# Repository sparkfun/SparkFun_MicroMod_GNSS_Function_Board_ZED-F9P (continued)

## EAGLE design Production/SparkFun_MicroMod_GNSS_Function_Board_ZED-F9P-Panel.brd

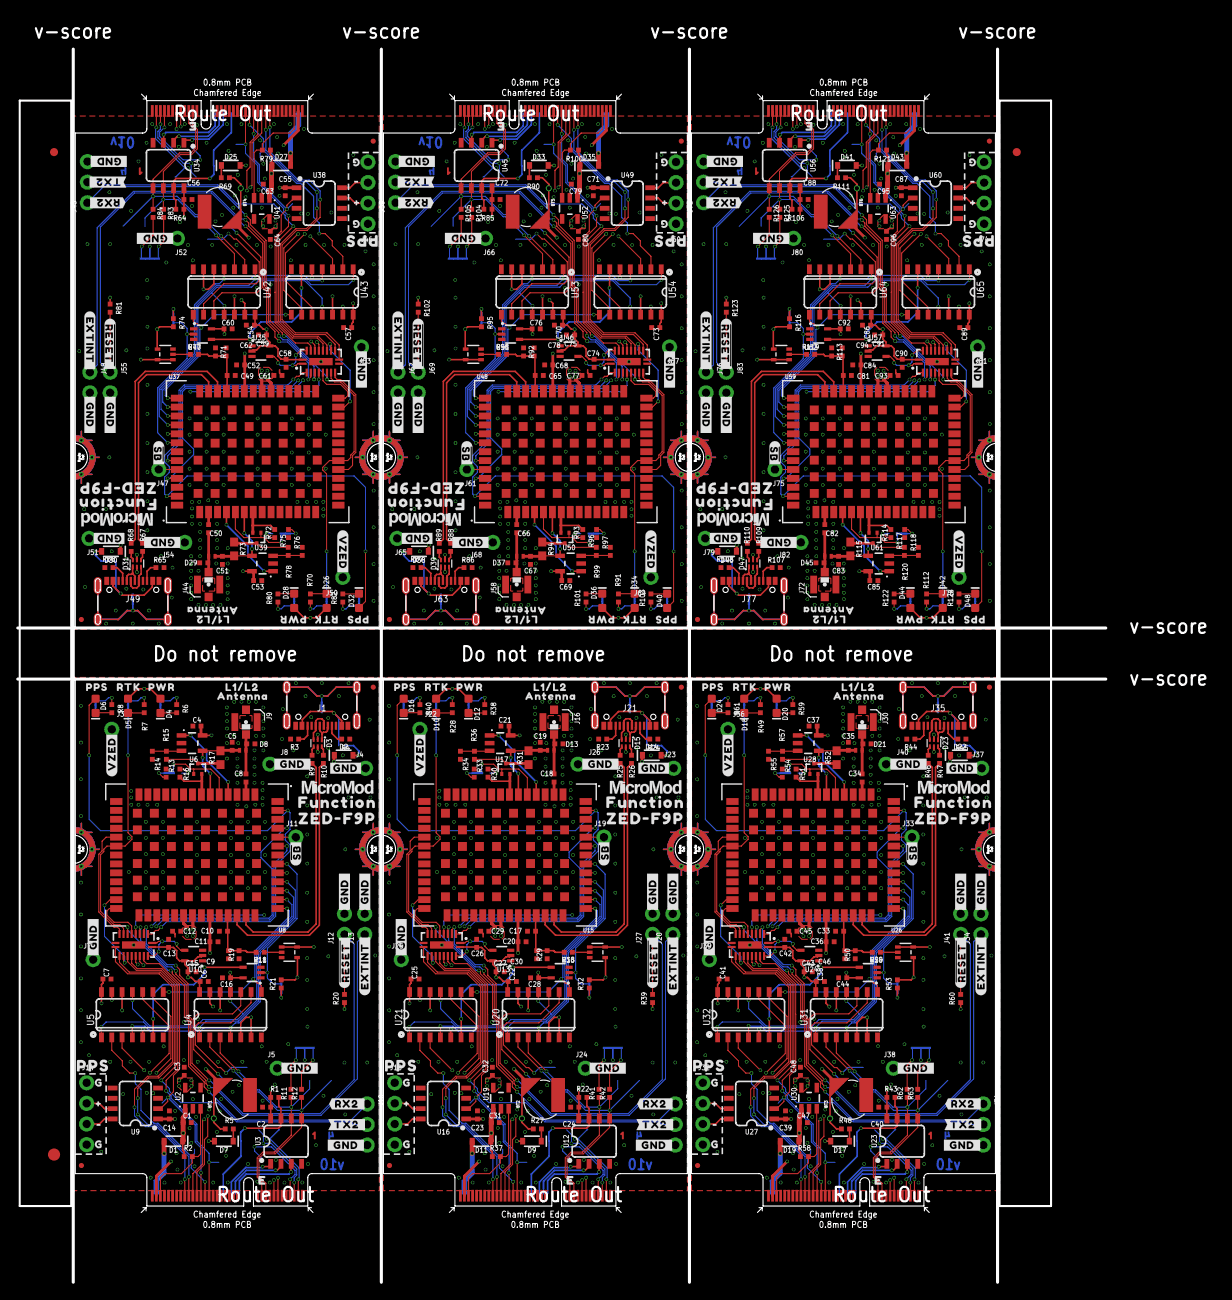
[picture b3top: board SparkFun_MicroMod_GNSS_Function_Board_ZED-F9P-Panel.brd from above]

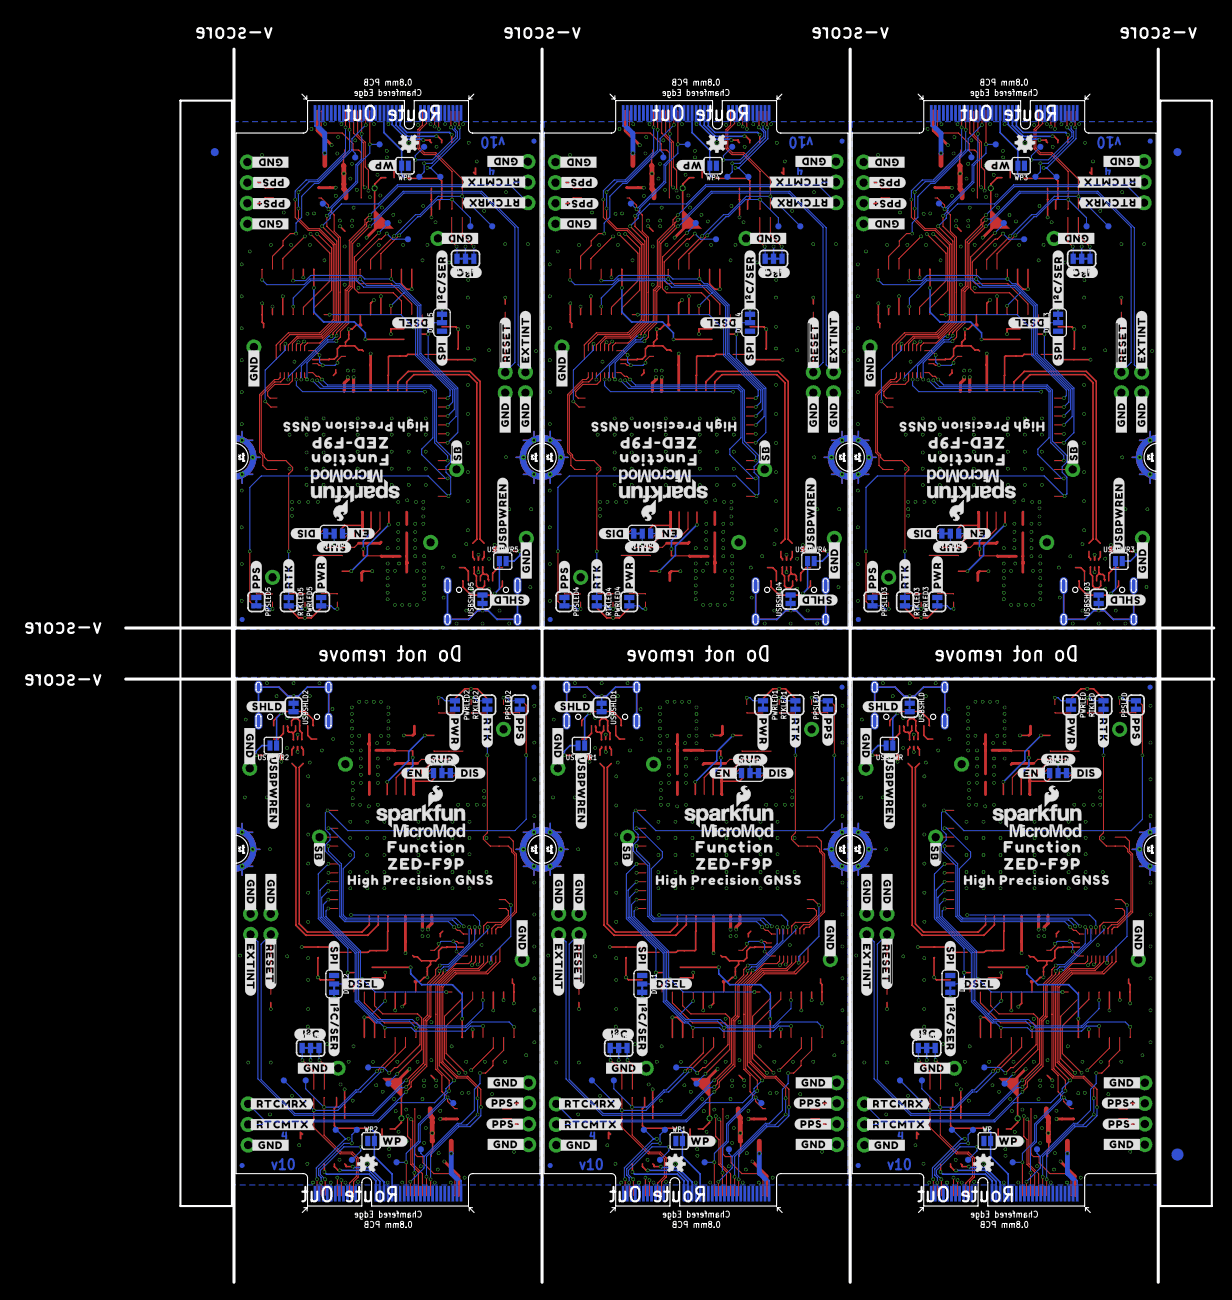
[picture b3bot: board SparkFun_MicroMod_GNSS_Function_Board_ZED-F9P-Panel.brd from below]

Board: 4 copper layers, 134.2 x 152.1 mm, 984 parts (339 on the bottom side), 468 nets.

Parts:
ANTSUP, ANTSUP1, ANTSUP2, ANTSUP3, ANTSUP4, ANTSUP5: JUMPER-SMT_3_1-NC_TRACE_SILK; SMT-JUMPER_3_1-NC_TRACE_SILK
BT1, BT2, BT3, BT4, BT5, BT6: RELOWABLE_BATTERY_MS421R; MS421R_IV03E
C1, C3, C9, C12, C29, C30, C31, C32, C45, C46, C47, C48, C61, C62, C63, C64, C77, C78, C79, C80, C93, C94, C95, C96: 1.0uF; 0402-TIGHT
C2, C4, C6, C7, C10, C13, C14, C15, C16, C17, C21, C22, C23, C24, C25, C26, C27, C28, C33, C37, C38, C39, C40, C41, C42, C43, C44, C49, C53, C54, C55, C56, C57, C58, C59, C60, C65, C69, C70, C71, C72, C73, C74, C75, C76, C81, C85, C86, C87, C88, C89, C90, C91, C92: 0.1uF; 0402-TIGHT
C5, C19, C35, C51, C67, C83: 10nF; 0402-TIGHT
C8, C18, C34, C50, C66, C82: 47pF; 0402-TIGHT
C11, C20, C36, C52, C68, C84: 2.2uF; 0402-TIGHT
D1, D2, D11, D14, D19, D22, D27, D30, D35, D38, D43, D46: 3A/10V/280mV; SOD-323
D3, D15, D23, D31, D39, D47: PRTR5V0U2F; SOT886
D4, D12, D20, D28, D36, D44: RED; LED-0603
D5, D6, D10, D16, D18, D24, D26, D32, D34, D40, D42, D48: BLUE; LED-0603
D7, D9, D17, D25, D33, D41: 0.5A/40V/420mV; SOD-323
D8, D13, D21, D29, D37, D45: PESD0402-0402T; 0402-TIGHT
DSEL, DSEL1, DSEL2, DSEL3, DSEL4, DSEL5: JUMPER-SMT_3_1-NC_TRACE_SILK; SMT-JUMPER_3_1-NC_TRACE_SILK
E$1, E$2, E$3, E$4: FIDUCIAL-1X2
E$5, E$6: FIDUCIAL-1.5X3
FD1, FD2, FD3, FD4, FD5, FD6, FD7, FD8, FD9, FD10, FD11, FD12, FD13, FD14, FD15, FD16, FD17, FD18, FD19, FD20, FD21, FD22, FD23, FD24: FIDUCIALUFIDUCIAL; FIDUCIAL-MICRO
FRAME1, FRAME2, FRAME3, FRAME4, FRAME5, FRAME6: FRAME-LEDGER; CREATIVE_COMMONS
I2CPUR, I2CPUR1, I2CPUR2, I2CPUR3, I2CPUR4, I2CPUR5: JUMPER-SMT_3_2-NC_TRACE_SILK; SMT-JUMPER_3_2-NC_TRACE_SILK
J1, J21, J35, J49, J63, J77: USB Female Type C Connector; USB-C-16P-4LAYER-ISOLATED
J2, J15, J29, J43, J57, J71: MICROMOD_FUNCTION_STANDARD; M.2-CARD-E-22_FUNCTION_STANDARD
J3, J4, J5, J7, J8, J11, J19, J22, J23, J24, J25, J26, J33, J36, J37, J38, J39, J40, J47, J50, J51, J52, J53, J54, J61, J64, J65, J66, J67, J68, J75, J78, J79, J80, J81, J82: 1X01_NO_SILK
J6, J28, J42, J56, J70, J84: 1X01_SMALL
J9, J16, J30, J44, J58, J72: U.FL
J10, J17, J31, J45, J59, J73: 455-1750-1-ND; 1X03_NO_SILK
J12, J13, J20, J27, J34, J41, J48, J55, J62, J69, J76, J83: 1X02_NO_SILK
J14, J18, J32, J46, J60, J74: 1X04_NO_SILK
L1, L2, L3, L4, L5, L6: 150nH; 0402_MURATA
LOGO1, LOGO6, LOGO9, LOGO12, LOGO15, LOGO18: SFE_LOGO_NAME_FLAMEBLANK; BLANK
LOGO2, LOGO3, LOGO7, LOGO10, LOGO13, LOGO16: OSHW-LOGOMINI; OSHW-LOGO-MINI
LOGO4, LOGO5, LOGO8, LOGO11, LOGO14, LOGO17: SFE_LOGO_NAME_FLAME.1_INCH; SFE_LOGO_NAME_FLAME_.1
PPSLED, PPSLED1, PPSLED2, PPSLED3, PPSLED4, PPSLED5: JUMPER-SMT_2_NC_TRACE_SILK; SMT-JUMPER_2_NC_TRACE_SILK
PWRLED, PWRLED1, PWRLED2, PWRLED3, PWRLED4, PWRLED5: JUMPER-SMT_2_NC_TRACE_SILK; SMT-JUMPER_2_NC_TRACE_SILK
Q1, Q2, Q3, Q4, Q5, Q6: DMP21D0UT-7; SOT523
R1, R2, R13, R14, R20, R21, R22, R32, R33, R34, R37, R39, R43, R53, R54, R55, R58, R60, R64, R74, R75, R76, R79, R81, R85, R95, R96, R97, R100, R102, R106, R116, R117, R118, R121, R123: 10k; 0402-TIGHT
R3, R4, R23, R24, R44, R45, R65, R66, R86, R87, R107, R108: 5.1k; 0402-TIGHT
R5, R27, R48, R69, R90, R111: 3.3K; 0402-TIGHT
R6, R15, R36, R38, R57, R59, R78, R80, R99, R101, R120, R122: 1k; 0402-TIGHT
R7, R8, R28, R40, R49, R61, R70, R82, R91, R103, R112, R124: 4.7k; 0402-TIGHT
R9, R10, R25, R26, R46, R47, R67, R68, R88, R89, R109, R110: 27; 0402-TIGHT
R11, R12, R41, R42, R62, R63, R83, R84, R104, R105, R125, R126: 2.2k; 0402-TIGHT
R16, R30, R51, R72, R93, R114: 100k; 0402-TIGHT
R17, R31, R52, R73, R94, R115: 10; 0603
R18, R35, R56, R77, R98, R119: 22k; 0402-TIGHT
R19, R29, R50, R71, R92, R113: 47k; 0402-TIGHT
RTKLED, RTKLED1, RTKLED2, RTKLED3, RTKLED4, RTKLED5: JUMPER-SMT_2_NC_TRACE_SILK; SMT-JUMPER_2_NC_TRACE_SILK
TP1, TP2, TP3, TP4, TP5, TP6, TP7, TP8, TP9, TP10, TP11, TP12, TP13, TP14, TP15, TP16, TP17, TP18, TP19, TP20, TP21, TP22, TP23, TP24, TP25, TP26, TP27, TP28, TP29, TP30, TP31, TP32, TP33, TP34, TP35, TP36, TP37, TP38, TP39, TP40, TP41, TP42, TP43, TP44, TP45, TP46, TP47, TP48, TP49, TP50, TP51, TP52, TP53, TP54, TP55, TP56, TP57, TP58, TP59, TP60: TEST-POINT3; PAD.03X.03
U1, U22, U33, U44, U55, U66: NLAST4501DFT2G; SOT353
U2, U19, U30, U41, U52, U63: 3.3V; SOT23-5
U3, U12, U23, U34, U45, U56: EEPROM; SO08
U4, U5, U20, U21, U31, U32, U42, U43, U53, U54, U64, U65: 74LVC4066D_QUAD_BILATERAL_SWITCH; SO14
U6, U17, U28, U39, U50, U61: OPA344; SOT23-5
U7, U14, U25, U36, U47, U58: 74LVC541A; DHVQFN20
U8, U15, U26, U37, U48, U59: U-BLOX_ZED-F9P; ZED-F9P
U9, U16, U27, U38, U49, U60: FIN1017MX; SO08
U10, U11, U13, U18, U24, U29, U35, U40, U46, U51, U57, U62: SN74AUP1T04; SC-70-5_DCK
U$1, U$119, U$182, U$245, U$308, U$371: 40
U$2, U$92, U$159, U$222, U$285, U$348: #_RTCMTX#0
U$3, U$93, U$160, U$223, U$286, U$349: #TX2_#0
U$4, U$8, U$37, U$63, U$127, U$128, U$190, U$191, U$253, U$254, U$316, U$317: MICROMOD_LOGO_.35
U$5, U$6, U$7, U$9, U$10, U$11, U$18, U$19, U$21, U$22, U$25, U$33, U$38, U$39, U$94, U$95, U$96, U$97, U$98, U$99, U$108, U$109, U$110, U$111, U$116, U$123, U$124, U$125, U$161, U$162, U$163, U$164, U$165, U$166, U$173, U$174, U$175, U$176, U$179, U$186, U$187, U$188, U$224, U$225, U$226, U$227, U$228, U$229, U$236, U$237, U$238, U$239, U$242, U$249, U$250, U$251, U$287, U$288, U$289, U$290, U$291, U$292, U$299, U$300, U$301, U$302, U$305, U$312, U$313, U$314, U$350, U$351, U$352, U$353, U$354, U$355, U$362, U$363, U$364, U$365, U$368, U$375, U$376, U$377: #_GND_#0
U$12, U$100, U$167, U$230, U$293, U$356: #_RTCMRX#0
U$13, U$101, U$168, U$231, U$294, U$357: #RX2_#0
U$14, U$102, U$169, U$232, U$295, U$358: ##RESET_##0
U$15, U$103, U$170, U$233, U$296, U$359: #_#RESET##0
U$16, U$105, U$171, U$234, U$297, U$360: #_EXTINT#0
U$17, U$107, U$172, U$235, U$298, U$361: #EXTINT_#0
U$20, U$26, U$27, U$41, U$129, U$130, U$192, U$193, U$255, U$256, U$318, U$319: FUNCTION0
U$23, U$113, U$177, U$240, U$303, U$366: #_I�C#SER#0
U$24, U$115, U$178, U$241, U$304, U$367: #SPI_#0
U$28, U$117, U$180, U$243, U$306, U$369: #_I�C#0
U$29, U$118, U$181, U$244, U$307, U$370: #_DSEL#0
U$30, U$120, U$183, U$246, U$309, U$372: #SUP#0
U$31, U$121, U$184, U$247, U$310, U$373: #RTK#0
U$32, U$122, U$185, U$248, U$311, U$374: #PWR#0
U$34, U$42, U$131, U$194, U$257, U$320: 10
U$35, U$43, U$132, U$195, U$258, U$321: 211
U$36, U$53, U$133, U$196, U$259, U$322: 3212
U$40, U$126, U$189, U$252, U$315, U$378: PPS3
U$44, U$60, U$139, U$202, U$265, U$328: #PPS##2252
U$45, U$61, U$140, U$203, U$266, U$329: #PPS##2253
U$46, U$47, U$55, U$56, U$134, U$135, U$197, U$198, U$260, U$261, U$323, U$324: G2
U$48, U$57, U$136, U$199, U$262, U$325: #3
U$49, U$58, U$137, U$200, U$263, U$326: #4
U$50, U$65, U$141, U$204, U$267, U$330: #PPS#2254
U$51, U$66, U$142, U$205, U$268, U$331: PPS0
U$52, U$67, U$143, U$206, U$269, U$332: RTK0
U$54, U$81, U$151, U$214, U$277, U$340: #WP#0
U$59, U$104, U$138, U$201, U$264, U$327: SFE_LOGO_FLAME_STOP_.1
U$62, U$70, U$145, U$208, U$271, U$334: #USBPWREN#10
U$64, U$71, U$146, U$209, U$272, U$335: #SHLD#12
U$68, U$89, U$156, U$219, U$282, U$345: #VZED#0
U$69, U$76, U$144, U$207, U$270, U$333: ##SB##9
U$72, U$79, U$150, U$213, U$276, U$339: PWR0
U$73, U$90, U$157, U$220, U$283, U$346: #_DIS#0
U$74, U$91, U$158, U$221, U$284, U$347: #EN_#0
U$75, U$106, U$147, U$210, U$273, U$336: HIGH_PRECISION_GNSS26
U$77, U$78, U$112, U$114, U$148, U$149, U$211, U$212, U$274, U$275, U$337, U$338: ZED#F9P0
U$80, U$83, U$152, U$215, U$278, U$341: ##SB##0
U$82, U$84, U$153, U$216, U$279, U$342: #GND#0
U$85, U$86, U$154, U$217, U$280, U$343: L1#L20
U$87, U$88, U$155, U$218, U$281, U$344: ANTENNA0
USBPWR, USBPWR1, USBPWR2, USBPWR3, USBPWR4, USBPWR5: JUMPER-SMT_2_NO_SILK; SMT-JUMPER_2_NO_SILK
USBSHLD, USBSHLD1, USBSHLD2, USBSHLD3, USBSHLD4, USBSHLD5: JUMPER-SMT_2_NC_TRACE_SILK; SMT-JUMPER_2_NC_TRACE_SILK
WP, WP1, WP2, WP3, WP4, WP5: JUMPER-SMT_2_NO_SILK; SMT-JUMPER_2_NO_SILK

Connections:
3.3V: C2.1, C14.1, D7.A, J2.73, R1.1, U3.8, U9.1
3.3V1: C23.1, C24.1, D9.A, J15.73, R22.1, U12.8, U16.1
3.3V2: C39.1, C40.1, D17.A, J29.73, R43.1, U23.8, U27.1
3.3V3: C55.1, C56.1, D25.A, J43.73, R64.1, U34.8, U38.1
3.3V4: C71.1, C72.1, D33.A, J57.73, R85.1, U45.8, U49.1
3.3V5: C87.1, C88.1, D41.A, J71.73, R106.1, U56.8, U60.1
5V: C1.1, D1.C, D2.C, R2.1, U2.1
5V1: C31.1, D11.C, D14.C, R37.1, U19.1
5V2: C47.1, D19.C, D22.C, R58.1, U30.1
5V3: C63.1, D27.C, D30.C, R79.1, U41.1
5V4: C79.1, D35.C, D38.C, R100.1, U52.1
5V5: C95.1, D43.C, D46.C, R121.1, U63.1
!RESET!: J2.53, J12.1, R20.2, U7.3
!RESET!1: J15.53, J27.1, R39.2, U14.3
!RESET!2: J29.53, J41.1, R60.2, U25.3
!RESET!3: J43.53, J55.1, R81.2, U36.3
!RESET!4: J57.53, J69.1, R102.2, U47.3
!RESET!5: J71.53, J83.1, R123.2, U58.3
!ZED_DSEL!: U5.5, U5.6, U5.12, U5.13, U11.4
!ZED_DSEL!1: U18.4, U21.5, U21.6, U21.12, U21.13
!ZED_DSEL!2: U29.4, U32.5, U32.6, U32.12, U32.13
!ZED_DSEL!3: U40.4, U43.5, U43.6, U43.12, U43.13
!ZED_DSEL!4: U51.4, U54.5, U54.6, U54.12, U54.13
!ZED_DSEL!5: U62.4, U65.5, U65.6, U65.12, U65.13
A0: J2.36, U3.1
A1: J2.34, U3.2
A2: J2.32, U3.3
A3: J15.36, U12.1
A4: J15.32, U12.3
A5: J15.34, U12.2
A6: J29.36, U23.1
A7: J29.32, U23.3
A8: J29.34, U23.2
A9: J43.36, U34.1
A10: J43.32, U34.3
A11: J43.34, U34.2
A12: J57.36, U45.1
A13: J57.32, U45.3
A14: J57.34, U45.2
A15: J71.36, U56.1
A16: J71.32, U56.3
A17: J71.34, U56.2
EWP: J2.40, R1.2, U3.7, WP.2
EWP1: J15.40, R22.2, U12.7, WP1.2
EWP2: J29.40, R43.2, U23.7, WP2.2
EWP3: J43.40, R64.2, U34.7, WP3.2
EWP4: J57.40, R85.2, U45.7, WP4.2
EWP5: J71.40, R106.2, U56.7, WP5.2
EXTINT: J2.55, J13.1, U7.4
EXTINT1: J15.55, J20.1, U14.4
EXTINT2: J29.55, J34.1, U25.4
EXTINT3: J43.55, J48.1, U36.4
EXTINT4: J57.55, J62.1, U47.4
EXTINT5: J71.55, J76.1, U58.4
GEO_STAT: J2.59, U7.11
GEO_STAT1: J15.59, U14.11
GEO_STAT2: J29.59, U25.11
GEO_STAT3: J43.59, U36.11
GEO_STAT4: J57.59, U47.11
GEO_STAT5: J71.59, U58.11
GND: BT1.-, C1.2, C2.2, C3.2, C4.2, C5.2, C6.2, C7.2, C9.2, C10.2, C11.2, C12.2, C13.2, C14.2, C15.2, C16.2, D3.2, D8.2, DSEL.1, J1.GND, J1.GND2, J2.1, J2.33, J2.39, J2.45, J2.75, J2.GND1, J2.GND2, J2.GND3, J2.GND4, J2.GND5, J2.GND6, J4.1, J5.1, J7.1, J8.1, J9.1, J9.2, J10.3, J12.2, J13.2, J14.1, J14.4, PPSLED.1, PWRLED.2, R3.1, R4.1, R14.1, R16.1, R19.1, U1.3, U2.2, U3.4, U4.7, U5.7, U6.2, U7.10, U7.EPAD, U8.1, U8.3, U8.12, U8.14, U8.32, U8.37, U8.41, U8.48, U8.55, U8.56, U8.57, U8.58, U8.59, U8.60, U8.61, U8.62, U8.63, U8.64, U8.65, U8.66, U8.67, U8.68, U8.69, U8.70, U8.71, U8.72, U8.73, U8.74, U8.75, U8.76, U8.77, U8.78, U8.79, U8.80, U8.81, U8.82, U8.83, U8.84, U8.85, U8.86, U8.87, U8.88, U8.89, U8.90, U8.91, U8.92, U8.93, U8.94, U8.95, U8.96, U8.97, U8.98, U8.99, U8.100, U8.101, U8.102, U9.4, U10.3, U11.3, USBSHLD.2, WP.1
GND1: BT2.-, C17.2, C19.2, C20.2, C21.2, C22.2, C23.2, C24.2, C25.2, C26.2, C27.2, C28.2, C29.2, C30.2, C31.2, C32.2, D13.2, D15.2, DSEL1.1, J15.1, J15.33, J15.39, J15.45, J15.75, J15.GND1, J15.GND2, J15.GND3, J15.GND4, J15.GND5, J15.GND6, J16.1, J16.2, J17.3, J18.1, J18.4, J20.2, J21.GND, J21.GND2, J23.1, J24.1, J25.1, J26.1, J27.2, PPSLED1.1, PWRLED1.2, R23.1, R24.1, R29.1, R30.1, R34.1, U12.4, U13.3, U14.10, U14.EPAD, U15.1, U15.3, U15.12, U15.14, U15.32, U15.37, U15.41, U15.48, U15.55, U15.56, U15.57, U15.58, U15.59, U15.60, U15.61, U15.62, U15.63, U15.64, U15.65, U15.66, U15.67, U15.68, U15.69, U15.70, U15.71, U15.72, U15.73, U15.74, U15.75, U15.76, U15.77, U15.78, U15.79, U15.80, U15.81, U15.82, U15.83, U15.84, U15.85, U15.86, U15.87, U15.88, U15.89, U15.90, U15.91, U15.92, U15.93, U15.94, U15.95, U15.96, U15.97, U15.98, U15.99, U15.100, U15.101, U15.102, U16.4, U17.2, U18.3, U19.2, U20.7, U21.7, U22.3, USBSHLD1.2, WP1.1
GND2: BT3.-, C33.2, C35.2, C36.2, C37.2, C38.2, C39.2, C40.2, C41.2, C42.2, C43.2, C44.2, C45.2, C46.2, C47.2, C48.2, D21.2, D23.2, DSEL2.1, J29.1, J29.33, J29.39, J29.45, J29.75, J29.GND1, J29.GND2, J29.GND3, J29.GND4, J29.GND5, J29.GND6, J30.1, J30.2, J31.3, J32.1, J32.4, J34.2, J35.GND, J35.GND2, J37.1, J38.1, J39.1, J40.1, J41.2, PPSLED2.1, PWRLED2.2, R44.1, R45.1, R50.1, R51.1, R55.1, U23.4, U24.3, U25.10, U25.EPAD, U26.1, U26.3, U26.12, U26.14, U26.32, U26.37, U26.41, U26.48, U26.55, U26.56, U26.57, U26.58, U26.59, U26.60, U26.61, U26.62, U26.63, U26.64, U26.65, U26.66, U26.67, U26.68, U26.69, U26.70, U26.71, U26.72, U26.73, U26.74, U26.75, U26.76, U26.77, U26.78, U26.79, U26.80, U26.81, U26.82, U26.83, U26.84, U26.85, U26.86, U26.87, U26.88, U26.89, U26.90, U26.91, U26.92, U26.93, U26.94, U26.95, U26.96, U26.97, U26.98, U26.99, U26.100, U26.101, U26.102, U27.4, U28.2, U29.3, U30.2, U31.7, U32.7, U33.3, USBSHLD2.2, WP2.1
GND3: BT4.-, C49.2, C51.2, C52.2, C53.2, C54.2, C55.2, C56.2, C57.2, C58.2, C59.2, C60.2, C61.2, C62.2, C63.2, C64.2, D29.2, D31.2, DSEL3.1, J43.1, J43.33, J43.39, J43.45, J43.75, J43.GND1, J43.GND2, J43.GND3, J43.GND4, J43.GND5, J43.GND6, J44.1, J44.2, J45.3, J46.1, J46.4, J48.2, J49.GND, J49.GND2, J51.1, J52.1, J53.1, J54.1, J55.2, PPSLED3.1, PWRLED3.2, R65.1, R66.1, R71.1, R72.1, R76.1, U34.4, U35.3, U36.10, U36.EPAD, U37.1, U37.3, U37.12, U37.14, U37.32, U37.37, U37.41, U37.48, U37.55, U37.56, U37.57, U37.58, U37.59, U37.60, U37.61, U37.62, U37.63, U37.64, U37.65, U37.66, U37.67, U37.68, U37.69, U37.70, U37.71, U37.72, U37.73, U37.74, U37.75, U37.76, U37.77, U37.78, U37.79, U37.80, U37.81, U37.82, U37.83, U37.84, U37.85, U37.86, U37.87, U37.88, U37.89, U37.90, U37.91, U37.92, U37.93, U37.94, U37.95, U37.96, U37.97, U37.98, U37.99, U37.100, U37.101, U37.102, U38.4, U39.2, U40.3, U41.2, U42.7, U43.7, U44.3, USBSHLD3.2, WP3.1
GND4: BT5.-, C65.2, C67.2, C68.2, C69.2, C70.2, C71.2, C72.2, C73.2, C74.2, C75.2, C76.2, C77.2, C78.2, C79.2, C80.2, D37.2, D39.2, DSEL4.1, J57.1, J57.33, J57.39, J57.45, J57.75, J57.GND1, J57.GND2, J57.GND3, J57.GND4, J57.GND5, J57.GND6, J58.1, J58.2, J59.3, J60.1, J60.4, J62.2, J63.GND, J63.GND2, J65.1, J66.1, J67.1, J68.1, J69.2, PPSLED4.1, PWRLED4.2, R86.1, R87.1, R92.1, R93.1, R97.1, U45.4, U46.3, U47.10, U47.EPAD, U48.1, U48.3, U48.12, U48.14, U48.32, U48.37, U48.41, U48.48, U48.55, U48.56, U48.57, U48.58, U48.59, U48.60, U48.61, U48.62, U48.63, U48.64, U48.65, U48.66, U48.67, U48.68, U48.69, U48.70, U48.71, U48.72, U48.73, U48.74, U48.75, U48.76, U48.77, U48.78, U48.79, U48.80, U48.81, U48.82, U48.83, U48.84, U48.85, U48.86, U48.87, U48.88, U48.89, U48.90, U48.91, U48.92, U48.93, U48.94, U48.95, U48.96, U48.97, U48.98, U48.99, U48.100, U48.101, U48.102, U49.4, U50.2, U51.3, U52.2, U53.7, U54.7, U55.3, USBSHLD4.2, WP4.1
GND5: BT6.-, C81.2, C83.2, C84.2, C85.2, C86.2, C87.2, C88.2, C89.2, C90.2, C91.2, C92.2, C93.2, C94.2, C95.2, C96.2, D45.2, D47.2, DSEL5.1, J71.1, J71.33, J71.39, J71.45, J71.75, J71.GND1, J71.GND2, J71.GND3, J71.GND4, J71.GND5, J71.GND6, J72.1, J72.2, J73.3, J74.1, J74.4, J76.2, J77.GND, J77.GND2, J79.1, J80.1, J81.1, J82.1, J83.2, PPSLED5.1, PWRLED5.2, R107.1, R108.1, R113.1, R114.1, R118.1, U56.4, U57.3, U58.10, U58.EPAD, U59.1, U59.3, U59.12, U59.14, U59.32, U59.37, U59.41, U59.48, U59.55, U59.56, U59.57, U59.58, U59.59, U59.60, U59.61, U59.62, U59.63, U59.64, U59.65, U59.66, U59.67, U59.68, U59.69, U59.70, U59.71, U59.72, U59.73, U59.74, U59.75, U59.76, U59.77, U59.78, U59.79, U59.80, U59.81, U59.82, U59.83, U59.84, U59.85, U59.86, U59.87, U59.88, U59.89, U59.90, U59.91, U59.92, U59.93, U59.94, U59.95, U59.96, U59.97, U59.98, U59.99, U59.100, U59.101, U59.102, U60.4, U61.2, U62.3, U63.2, U64.7, U65.7, U66.3, USBSHLD5.2, WP5.1
IO_!OE!: U7.1, U7.19, U10.4
IO_!OE!1: U13.4, U14.1, U14.19
IO_!OE!2: U24.4, U25.1, U25.19
IO_!OE!3: U35.4, U36.1, U36.19
IO_!OE!4: U46.4, U47.1, U47.19
IO_!OE!5: U57.4, U58.1, U58.19
MM_!CS!: J2.49, TP11.1, U5.2
MM_!CS!1: J15.49, TP19.1, U21.2
MM_!CS!2: J29.49, TP29.1, U32.2
MM_!CS!3: J43.49, TP39.1, U43.2
MM_!CS!4: J57.49, TP49.1, U54.2
MM_!CS!5: J71.49, TP59.1, U65.2
MM_PICO: J2.5, TP12.1, U5.10
MM_PICO1: J15.5, TP16.1, U21.10
MM_PICO2: J29.5, TP26.1, U32.10
MM_PICO3: J43.5, TP36.1, U43.10
MM_PICO4: J57.5, TP46.1, U54.10
MM_PICO5: J71.5, TP56.1, U65.10
MM_POCI: J2.7, TP13.1, U5.9
MM_POCI1: J15.7, TP17.1, U21.9
MM_POCI2: J29.7, TP27.1, U32.9
MM_POCI3: J43.7, TP37.1, U43.9
MM_POCI4: J57.7, TP47.1, U54.9
MM_POCI5: J71.7, TP57.1, U65.9
MM_RX: J2.15, TP7.1, U4.10
MM_RX1: J15.15, TP2.1, U20.10
MM_RX2: J29.15, TP22.1, U31.10
MM_RX3: J43.15, TP32.1, U42.10
MM_RX4: J57.15, TP42.1, U53.10
MM_RX5: J71.15, TP52.1, U64.10
MM_SCK: J2.3, TP10.1, U5.3
MM_SCK1: J15.3, TP18.1, U21.3
MM_SCK2: J29.3, TP28.1, U32.3
MM_SCK3: J43.3, TP38.1, U43.3
MM_SCK4: J57.3, TP48.1, U54.3
MM_SCK5: J71.3, TP58.1, U65.3
MM_SCL: J2.21, R11.1, TP5.1, U3.6, U4.3
MM_SCL1: J15.21, R41.1, TP4.1, U12.6, U20.3
MM_SCL2: J29.21, R62.1, TP24.1, U23.6, U31.3
MM_SCL3: J43.21, R83.1, TP34.1, U34.6, U42.3
MM_SCL4: J57.21, R104.1, TP44.1, U45.6, U53.3
MM_SCL5: J71.21, R125.1, TP54.1, U56.6, U64.3
MM_SDA: J2.19, R12.1, TP6.1, U3.5, U4.2
MM_SDA1: J15.19, R42.1, TP15.1, U12.5, U20.2
MM_SDA2: J29.19, R63.1, TP25.1, U23.5, U31.2
MM_SDA3: J43.19, R84.1, TP35.1, U34.5, U42.2
MM_SDA4: J57.19, R105.1, TP45.1, U45.5, U53.2
MM_SDA5: J71.19, R126.1, TP55.1, U56.5, U64.2
MM_TX: J2.13, TP8.1, U4.9
MM_TX1: J15.13, TP3.1, U20.9
MM_TX2: J29.13, TP23.1, U31.9
MM_TX3: J43.13, TP33.1, U42.9
MM_TX4: J57.13, TP43.1, U53.9
MM_TX5: J71.13, TP53.1, U64.9
unnamed: ANTSUP.1, R13.1
unnamed: ANTSUP.3, R14.2
unnamed: J1.B5, R3.2
unnamed: J1.A5, R4.2
unnamed: DSEL.3, R21.1
unnamed: I2CPUR.3, R11.2
unnamed: C8.1, D8.1, J9.FEED, L1.2
unnamed: R7.1, RTKLED.2
unnamed: I2CPUR.1, R12.2
unnamed: J21.B5, R23.2
unnamed: J21.A5, R24.2
unnamed: D9.C, R27.2
unnamed: Q1.1, R15.1, R17.1
unnamed: C9.1, C10.1, R18.2, R19.2, U8.38
unnamed: R28.1, RTKLED1.2
unnamed: D2.A, USBPWR.2
unnamed: D10.C, R28.2
unnamed: PWRLED1.1, R38.1
unnamed: D12.C, R38.2
unnamed: R30.2, R36.2, U17.3
unnamed: Q2.1, R31.1, R36.1
unnamed: C18.1, D13.1, J16.FEED, L2.2
unnamed: D14.A, USBPWR1.2
unnamed: C17.1, C30.1, R29.2, R35.2, U15.38
unnamed: ANTSUP1.1, R33.1
unnamed: PWRLED.1, R6.1
unnamed: PPSLED.2, R8.1
unnamed: D6.C, R8.2
unnamed: D5.C, R7.2
unnamed: D4.C, R6.2
unnamed: ANTSUP1.3, R34.2
unnamed: D7.C, R5.2
unnamed: DSEL1.3, R32.1
unnamed: PPSLED1.2, R40.1
unnamed: D16.C, R40.2
unnamed: I2CPUR1.3, R41.2
unnamed: I2CPUR1.1, R42.2
unnamed: J35.B5, R44.2
unnamed: J35.A5, R45.2
unnamed: D17.C, R48.2
unnamed: R49.1, RTKLED2.2
unnamed: D18.C, R49.2
unnamed: PWRLED2.1, R59.1
unnamed: D20.C, R59.2
unnamed: R51.2, R57.2, U28.3
unnamed: Q3.1, R52.1, R57.1
unnamed: C34.1, D21.1, J30.FEED, L3.2
unnamed: R15.2, R16.2, U6.3
unnamed: D22.A, USBPWR2.2
unnamed: C33.1, C46.1, R50.2, R56.2, U26.38
unnamed: ANTSUP2.1, R54.1
unnamed: ANTSUP2.3, R55.2
unnamed: DSEL2.3, R53.1
unnamed: PPSLED2.2, R61.1
unnamed: D24.C, R61.2
unnamed: I2CPUR2.3, R62.2
unnamed: I2CPUR2.1, R63.2
unnamed: J49.B5, R65.2
unnamed: J49.A5, R66.2
unnamed: D25.C, R69.2
unnamed: R70.1, RTKLED3.2
unnamed: D26.C, R70.2
unnamed: PWRLED3.1, R80.1
unnamed: D28.C, R80.2
unnamed: R72.2, R78.2, U39.3
unnamed: Q4.1, R73.1, R78.1
unnamed: C50.1, D29.1, J44.FEED, L4.2
unnamed: D30.A, USBPWR3.2
unnamed: C49.1, C62.1, R71.2, R77.2, U37.38
unnamed: ANTSUP3.1, R75.1
unnamed: ANTSUP3.3, R76.2
unnamed: DSEL3.3, R74.1
unnamed: PPSLED3.2, R82.1
unnamed: D32.C, R82.2
unnamed: I2CPUR3.3, R83.2
unnamed: I2CPUR3.1, R84.2
unnamed: J63.B5, R86.2
unnamed: J63.A5, R87.2
unnamed: D33.C, R90.2
unnamed: R91.1, RTKLED4.2
unnamed: D34.C, R91.2
unnamed: PWRLED4.1, R101.1
unnamed: D36.C, R101.2
unnamed: R93.2, R99.2, U50.3
unnamed: Q5.1, R94.1, R99.1
unnamed: C66.1, D37.1, J58.FEED, L5.2
unnamed: D38.A, USBPWR4.2
unnamed: C65.1, C78.1, R92.2, R98.2, U48.38
unnamed: ANTSUP4.1, R96.1
unnamed: ANTSUP4.3, R97.2
unnamed: DSEL4.3, R95.1
unnamed: PPSLED4.2, R103.1
unnamed: D40.C, R103.2
unnamed: I2CPUR4.3, R104.2
unnamed: I2CPUR4.1, R105.2
unnamed: J77.B5, R107.2
unnamed: J77.A5, R108.2
unnamed: D41.C, R111.2
unnamed: R112.1, RTKLED5.2
unnamed: D42.C, R112.2
unnamed: PWRLED5.1, R122.1
unnamed: D44.C, R122.2
unnamed: R114.2, R120.2, U61.3
unnamed: Q6.1, R115.1, R120.1
unnamed: C82.1, D45.1, J72.FEED, L6.2
unnamed: D46.A, USBPWR5.2
unnamed: C81.1, C94.1, R113.2, R119.2, U59.38
unnamed: ANTSUP5.1, R117.1
unnamed: ANTSUP5.3, R118.2
unnamed: DSEL5.3, R116.1
unnamed: PPSLED5.2, R124.1
unnamed: D48.C, R124.2
unnamed: I2CPUR5.3, R125.2
unnamed: I2CPUR5.1, R126.2
PPS: J2.51, TP9.1, U7.18, U9.2
PPS1: J15.51, TP1.1, U14.18, U16.2
PPS2: J29.51, TP21.1, U25.18, U27.2
PPS3: J43.51, TP31.1, U36.18, U38.2
PPS4: J57.51, TP41.1, U47.18, U49.2
PPS5: J71.51, TP51.1, U58.18, U60.2
PPS_DIFF_N: J14.3, U9.8
PPS_DIFF_N1: J18.3, U16.8
PPS_DIFF_N2: J32.3, U27.8
PPS_DIFF_N3: J46.3, U38.8
PPS_DIFF_N4: J60.3, U49.8
PPS_DIFF_N5: J74.3, U60.8
PPS_DIFF_P: J14.2, U9.7
PPS_DIFF_P1: J18.2, U16.7
PPS_DIFF_P2: J32.2, U27.7
PPS_DIFF_P3: J46.2, U38.7
PPS_DIFF_P4: J60.2, U49.7
PPS_DIFF_P5: J74.2, U60.7
PWR_EN: J2.71, R2.2, U2.3
PWR_EN1: J15.71, R37.2, U19.3
PWR_EN2: J29.71, R58.2, U30.3
PWR_EN3: J43.71, R79.2, U41.3
PWR_EN4: J57.71, R100.2, U52.3
PWR_EN5: J71.71, R121.2, U63.3
RF_IN: C8.2, U8.2
RF_IN1: C18.2, U15.2
RF_IN2: C34.2, U26.2
RF_IN3: C50.2, U37.2
RF_IN4: C66.2, U48.2
RF_IN5: C82.2, U59.2
RTK_STAT: J2.57, U7.12
RTK_STAT1: J15.57, U14.12
RTK_STAT2: J29.57, U25.12
RTK_STAT3: J43.57, U36.12
RTK_STAT4: J57.57, U47.12
RTK_STAT5: J71.57, U58.12
RX2/RTCM: J10.1, U7.7
RX2/RTCM1: J17.1, U14.7
RX2/RTCM2: J31.1, U25.7
RX2/RTCM3: J45.1, U36.7
RX2/RTCM4: J59.1, U47.7
RX2/RTCM5: J73.1, U58.7
SHLD: J1.SHLD1, J1.SHLD2, J1.SHLD3, J1.SHLD4, J1.SHLD5, J1.SHLD6, J1.SHLD7, J1.SHLD8, USBSHLD.1
SHLD1: J21.SHLD1, J21.SHLD2, J21.SHLD3, J21.SHLD4, J21.SHLD5, J21.SHLD6, J21.SHLD7, J21.SHLD8, USBSHLD1.1
SHLD2: J35.SHLD1, J35.SHLD2, J35.SHLD3, J35.SHLD4, J35.SHLD5, J35.SHLD6, J35.SHLD7, J35.SHLD8, USBSHLD2.1
SHLD3: J49.SHLD1, J49.SHLD2, J49.SHLD3, J49.SHLD4, J49.SHLD5, J49.SHLD6, J49.SHLD7, J49.SHLD8, USBSHLD3.1
SHLD4: J63.SHLD1, J63.SHLD2, J63.SHLD3, J63.SHLD4, J63.SHLD5, J63.SHLD6, J63.SHLD7, J63.SHLD8, USBSHLD4.1
SHLD5: J77.SHLD1, J77.SHLD2, J77.SHLD3, J77.SHLD4, J77.SHLD5, J77.SHLD6, J77.SHLD7, J77.SHLD8, USBSHLD5.1
TX2/RTCM: J10.2, U7.14
TX2/RTCM1: J17.2, U14.14
TX2/RTCM2: J31.2, U25.14
TX2/RTCM3: J45.2, U36.14
TX2/RTCM4: J59.2, U47.14
TX2/RTCM5: J73.2, U58.14
TX_READY: J2.47, TP14.1, U7.15
TX_READY1: J15.47, TP20.1, U14.15
TX_READY2: J29.47, TP30.1, U25.15
TX_READY3: J43.47, TP40.1, U36.15
TX_READY4: J57.47, TP50.1, U47.15
TX_READY5: J71.47, TP60.1, U58.15
USBC_N: D3.1, J1.A7, J1.B7
USBC_N1: D15.1, J21.A7, J21.B7
USBC_N2: D23.1, J35.A7, J35.B7
USBC_N3: D31.1, J49.A7, J49.B7
USBC_N4: D39.1, J63.A7, J63.B7
USBC_N5: D47.1, J77.A7, J77.B7
USBC_P: D3.3, J1.A6, J1.B6
USBC_P1: D15.3, J21.A6, J21.B6
USBC_P2: D23.3, J35.A6, J35.B6
USBC_P3: D31.3, J49.A6, J49.B6
USBC_P4: D39.3, J63.A6, J63.B6
USBC_P5: D47.3, J77.A6, J77.B6
USB_N: D3.6, R10.1
USB_N1: D15.6, R26.1
USB_N2: D23.6, R47.1
USB_N3: D31.6, R68.1
USB_N4: D39.6, R89.1
USB_N5: D47.6, R110.1
USB_P: D3.4, R9.1
USB_P1: D15.4, R25.1
USB_P2: D23.4, R46.1
USB_P3: D31.4, R67.1
USB_P4: D39.4, R88.1
USB_P5: D47.4, R109.1
VIN: D1.A, J2.72, J2.74
VIN1: D11.A, J15.72, J15.74
VIN2: D19.A, J29.72, J29.74
VIN3: D27.A, J43.72, J43.74
VIN4: D35.A, J57.72, J57.74
VIN5: D43.A, J71.72, J71.74
V_BATT: BT1.+, C11.1, J6.P$1, R5.1, U8.36
V_BATT1: BT2.+, C20.1, J28.P$1, R27.1, U15.36
V_BATT2: BT3.+, C36.1, J42.P$1, R48.1, U26.36
V_BATT3: BT4.+, C52.1, J56.P$1, R69.1, U37.36
V_BATT4: BT5.+, C68.1, J70.P$1, R90.1, U48.36
V_BATT5: BT6.+, C84.1, J84.P$1, R111.1, U59.36
V_RF: Q1.2, R13.2, U8.7
V_RF1: Q2.2, R33.2, U15.7
V_RF2: Q3.2, R54.2, U26.7
V_RF3: Q4.2, R75.2, U37.7
V_RF4: Q5.2, R96.2, U48.7
V_RF5: Q6.2, R117.2, U59.7
V_USB: D3.5, J1.VBUS1, J1.VBUS2, U1.1, U1.5, USBPWR.1
V_USB1: D15.5, J21.VBUS1, J21.VBUS2, U22.1, U22.5, USBPWR1.1
V_USB2: D23.5, J35.VBUS1, J35.VBUS2, U33.1, U33.5, USBPWR2.1
V_USB3: D31.5, J49.VBUS1, J49.VBUS2, U44.1, U44.5, USBPWR3.1
V_USB4: D39.5, J63.VBUS1, J63.VBUS2, U55.1, U55.5, USBPWR4.1
V_USB5: D47.5, J77.VBUS1, J77.VBUS2, U66.1, U66.5, USBPWR5.1
V_ZED: C3.1, C4.1, C6.1, C7.1, C12.1, C13.1, C15.1, C16.1, D4.A, D5.A, I2CPUR.2, J3.1, R20.1, R21.2, U1.4, U2.5, U4.14, U5.14, U6.5, U7.20, U8.33, U8.34, U10.2, U10.5, U11.5
V_ZED1: C21.1, C22.1, C25.1, C26.1, C27.1, C28.1, C29.1, C32.1, D10.A, D12.A, I2CPUR1.2, J22.1, R32.2, R39.1, U13.2, U13.5, U14.20, U15.33, U15.34, U17.5, U18.5, U19.5, U20.14, U21.14, U22.4
V_ZED2: C37.1, C38.1, C41.1, C42.1, C43.1, C44.1, C45.1, C48.1, D18.A, D20.A, I2CPUR2.2, J36.1, R53.2, R60.1, U24.2, U24.5, U25.20, U26.33, U26.34, U28.5, U29.5, U30.5, U31.14, U32.14, U33.4
V_ZED3: C53.1, C54.1, C57.1, C58.1, C59.1, C60.1, C61.1, C64.1, D26.A, D28.A, I2CPUR3.2, J50.1, R74.2, R81.1, U35.2, U35.5, U36.20, U37.33, U37.34, U39.5, U40.5, U41.5, U42.14, U43.14, U44.4
V_ZED4: C69.1, C70.1, C73.1, C74.1, C75.1, C76.1, C77.1, C80.1, D34.A, D36.A, I2CPUR4.2, J64.1, R95.2, R102.1, U46.2, U46.5, U47.20, U48.33, U48.34, U50.5, U51.5, U52.5, U53.14, U54.14, U55.4
V_ZED5: C85.1, C86.1, C89.1, C90.1, C91.1, C92.1, C93.1, C96.1, D42.A, D44.A, I2CPUR5.2, J78.1, R116.2, R123.1, U57.2, U57.5, U58.20, U59.33, U59.34, U61.5, U62.5, U63.5, U64.14, U65.14, U66.4
ZED_!RESET!: U7.17, U8.49
ZED_!RESET!1: U14.17, U15.49
ZED_!RESET!2: U25.17, U26.49
ZED_!RESET!3: U36.17, U37.49
ZED_!RESET!4: U47.17, U48.49
ZED_!RESET!5: U58.17, U59.49
ZED_!SAFEBOOT!: J11.1, U8.50
ZED_!SAFEBOOT!1: J19.1, U15.50
ZED_!SAFEBOOT!2: J33.1, U26.50
ZED_!SAFEBOOT!3: J47.1, U37.50
ZED_!SAFEBOOT!4: J61.1, U48.50
ZED_!SAFEBOOT!5: J75.1, U59.50
ZED_ANT_!SHORT!: C5.1, L1.1, R17.2, U6.4, U8.6
ZED_ANT_!SHORT!1: C19.1, L2.1, R31.2, U15.6, U17.4
ZED_ANT_!SHORT!2: C35.1, L3.1, R52.2, U26.6, U28.4
ZED_ANT_!SHORT!3: C51.1, L4.1, R73.2, U37.6, U39.4
ZED_ANT_!SHORT!4: C67.1, L5.1, R94.2, U48.6, U50.4
ZED_ANT_!SHORT!5: C83.1, L6.1, R115.2, U59.6, U61.4
ZED_ANT_DETECT: U6.1, U8.4
ZED_ANT_DETECT1: U15.4, U17.1
ZED_ANT_DETECT2: U26.4, U28.1
ZED_ANT_DETECT3: U37.4, U39.1
ZED_ANT_DETECT4: U48.4, U50.1
ZED_ANT_DETECT5: U59.4, U61.1
ZED_ANT_OFF: ANTSUP.2, Q1.3, U8.5
ZED_ANT_OFF1: ANTSUP1.2, Q2.3, U15.5
ZED_ANT_OFF2: ANTSUP2.2, Q3.3, U26.5
ZED_ANT_OFF3: ANTSUP3.2, Q4.3, U37.5
ZED_ANT_OFF4: ANTSUP4.2, Q5.3, U48.5
ZED_ANT_OFF5: ANTSUP5.2, Q6.3, U59.5
ZED_DSEL: DSEL.2, U4.5, U4.6, U4.12, U4.13, U8.47, U11.2
ZED_DSEL1: DSEL1.2, U15.47, U18.2, U20.5, U20.6, U20.12, U20.13
ZED_DSEL2: DSEL2.2, U26.47, U29.2, U31.5, U31.6, U31.12, U31.13
ZED_DSEL3: DSEL3.2, U37.47, U40.2, U42.5, U42.6, U42.12, U42.13
ZED_DSEL4: DSEL4.2, U48.47, U51.2, U53.5, U53.6, U53.12, U53.13
ZED_DSEL5: DSEL5.2, U59.47, U62.2, U64.5, U64.6, U64.12, U64.13
ZED_EXTINT: U7.16, U8.51
ZED_EXTINT1: U14.16, U15.51
ZED_EXTINT2: U25.16, U26.51
ZED_EXTINT3: U36.16, U37.51
ZED_EXTINT4: U47.16, U48.51
ZED_EXTINT5: U58.16, U59.51
ZED_GEO_STAT: U7.9, U8.19
ZED_GEO_STAT1: U14.9, U15.19
ZED_GEO_STAT2: U25.9, U26.19
ZED_GEO_STAT3: U36.9, U37.19
ZED_GEO_STAT4: U47.9, U48.19
ZED_GEO_STAT5: U58.9, U59.19
ZED_PPS: D6.A, U7.2, U8.53
ZED_PPS1: D16.A, U14.2, U15.53
ZED_PPS2: D24.A, U25.2, U26.53
ZED_PPS3: D32.A, U36.2, U37.53
ZED_PPS4: D40.A, U47.2, U48.53
ZED_PPS5: D48.A, U58.2, U59.53
ZED_RTK_STAT: RTKLED.1, U7.8, U8.20
ZED_RTK_STAT1: RTKLED1.1, U14.8, U15.20
ZED_RTK_STAT2: RTKLED2.1, U25.8, U26.20
ZED_RTK_STAT3: RTKLED3.1, U36.8, U37.20
ZED_RTK_STAT4: RTKLED4.1, U47.8, U48.20
ZED_RTK_STAT5: RTKLED5.1, U58.8, U59.20
ZED_RX2/RTCM: U7.13, U8.26
ZED_RX2/RTCM1: U14.13, U15.26
ZED_RX2/RTCM2: U25.13, U26.26
ZED_RX2/RTCM3: U36.13, U37.26
ZED_RX2/RTCM4: U47.13, U48.26
ZED_RX2/RTCM5: U58.13, U59.26
ZED_RX/PICO: U4.11, U5.11, U8.43
ZED_RX/PICO1: U15.43, U20.11, U21.11
ZED_RX/PICO2: U26.43, U31.11, U32.11
ZED_RX/PICO3: U37.43, U42.11, U43.11
ZED_RX/PICO4: U48.43, U53.11, U54.11
ZED_RX/PICO5: U59.43, U64.11, U65.11
ZED_SCL/SCK: U4.4, U5.4, U8.45
ZED_SCL/SCK1: U15.45, U20.4, U21.4
ZED_SCL/SCK2: U26.45, U31.4, U32.4
ZED_SCL/SCK3: U37.45, U42.4, U43.4
ZED_SCL/SCK4: U48.45, U53.4, U54.4
ZED_SCL/SCK5: U59.45, U64.4, U65.4
ZED_SDA/!CS!: U4.1, U5.1, U8.44
ZED_SDA/!CS!1: U15.44, U20.1, U21.1
ZED_SDA/!CS!2: U26.44, U31.1, U32.1
ZED_SDA/!CS!3: U37.44, U42.1, U43.1
ZED_SDA/!CS!4: U48.44, U53.1, U54.1
ZED_SDA/!CS!5: U59.44, U64.1, U65.1
ZED_TX2/RTCM: U7.6, U8.27
ZED_TX2/RTCM1: U14.6, U15.27
ZED_TX2/RTCM2: U25.6, U26.27
ZED_TX2/RTCM3: U36.6, U37.27
ZED_TX2/RTCM4: U47.6, U48.27
ZED_TX2/RTCM5: U58.6, U59.27
ZED_TX/POCI: U4.8, U5.8, U8.42
ZED_TX/POCI1: U15.42, U20.8, U21.8
ZED_TX/POCI2: U26.42, U31.8, U32.8
ZED_TX/POCI3: U37.42, U42.8, U43.8
ZED_TX/POCI4: U48.42, U53.8, U54.8
ZED_TX/POCI5: U59.42, U64.8, U65.8
ZED_TX_READY: U7.5, U8.46
ZED_TX_READY1: U14.5, U15.46
ZED_TX_READY2: U25.5, U26.46
ZED_TX_READY3: U36.5, U37.46
ZED_TX_READY4: U47.5, U48.46
ZED_TX_READY5: U58.5, U59.46
ZED_USB_DET: R18.1, U1.2
ZED_USB_DET1: R35.1, U22.2
ZED_USB_DET2: R56.1, U33.2
ZED_USB_DET3: R77.1, U44.2
ZED_USB_DET4: R98.1, U55.2
ZED_USB_DET5: R119.1, U66.2
ZED_USB_N: R10.2, U8.39
ZED_USB_N1: R26.2, U15.39
ZED_USB_N2: R47.2, U26.39
ZED_USB_N3: R68.2, U37.39
ZED_USB_N4: R89.2, U48.39
ZED_USB_N5: R110.2, U59.39
ZED_USB_P: R9.2, U8.40
ZED_USB_P1: R25.2, U15.40
ZED_USB_P2: R46.2, U26.40
ZED_USB_P3: R67.2, U37.40
ZED_USB_P4: R88.2, U48.40
ZED_USB_P5: R109.2, U59.40

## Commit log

2022-03-10 Added Documentation
2022-03-10 Created blank hardware files.
2022-03-14 Added EEPROM. Added LEDs. Added Module. Added Backup Battery. Added USB-C connector. Added Qwiic connector. Added GNSS App Note.
2022-03-15 Add Bug Report issue template.
2022-03-15 Update issue templates
    Add Feature Request Issue Template. Add 'bug' tag to Bug Report Issue Template.
2022-03-15 Update Feature Request issue template
2022-03-15 Update feature_request.md
    Fixed link to contribution page.
2022-03-15 Updated Readme, deleted old issue template file.
2022-03-16 Added I2C protection for ZED_F9P
2022-03-18 Created local library. Added ZED-F9P to sch.
    Created Local library.
    Added inverter to lib.
    Added octal buffer to lib.
    Added modified ZED-F9P to lib.
    Added ZED-F9P to sch.
2022-03-19 Filled out octal buffers, labeled nets. Modified inverter sch symbol.
2022-03-19 Renamed temp library to meet naming conventions.
2022-03-19 Added I/O and passives. Changed net names.
    Added passives surrounding IC's.
    Modified names to be more descriptive.
    Reorganized schematic for visual representation.
    Added Descriptions of schematic symbols.
2022-03-21 Completed antenna supervisor. Started External Antenna Power.
2022-03-22 Update ZED-F9P Integration Manual.
2022-03-23 Commit for current progress.
    Committing so others can begin a schematic review while I finish up.
2022-03-24 Schematic V1.0
2022-03-24 Added Correct Version to sch.
2022-03-25 Changed power resistor, needed higher power rating.
2022-03-25 Ran ERC and updated.
    Needed to re-place U3 parts. Needed to approve warnings/errors.
2022-03-25 Updated Schematic for ERC and comments from Paul.
    Created NO jumper on USB-C shield/gnd tie.
    Updated some power connections for style.
    Deleted $ from designations.
    Reworded ANT_OFF comment.
    Repositioned ANT_!SHORT! net.
    Floated U9Y7 output.
2022-03-28 Update Post schematic review.
    Made all easy changes, in midst of redoing decoupling per requests.
2022-03-30 Complete schematic after DR changes.
    Reorganized power: changed supply, removed fuse, replaced usb_det supply with voltage divider, renamed power nets.
    Added TPs and PTH breakouts for some pins.
    Changed I/O decoupling: Replaced octal buffer with 2x quad SSR switches, removed buffer on antenna supervision, rearranged pins on remaining octal buffer.
    Labeled diff PPS signal.
    Added second Qwiic connector.
    Added selector headers for bus and antenna supervisor circuits.
2022-03-30 Update selector wording per PC.
2022-03-30 ERC run and fixes applied.
    Forgot to do that before previous commit.
2022-03-31 First day of layout.
    Laid out most of the board with airwires. Have a rough idea of grounding so far so good. Have had to replace a fair bit of components for smaller ones. Those 0603's look massive on such a small board.
2022-03-31 Everything tentatively placed on board.
2022-03-31 1st draft power planes.
    Added split power planes to layout on inner layers.
2022-04-11 Board updates from time off.
    Airport board layout was time well spent.
2022-04-12 Removed extra copper in 2 parts.
2022-04-12 Update sch after fixing lib.
2022-04-12 End of day commit.
    Rearchitected plane placement based on rank.
    Began routing digital signals to end points.
2022-04-12 Replace backup battery.
    New part now in use.
2022-04-12 All traces routed.
    All traces routed, now need to just finish up via stitching, grounding, then silks.
2022-04-12 Change net class for vbatt.
2022-04-13 GND stitching and grounding complete.
    Outer GND plane stitching complete.
2022-04-13 Stitching of GND_RF complete.
2022-04-14 Passed DRC.
2022-04-15 End of Day commit.
    Got Buzzard working. Added a couple labels.
2022-04-15 Silks complete.
2022-04-18 Update New Parts Lib.
    Added missing information for new parts to get them ready to be part of normal libraries. Updated schematic and board accordingly.
2022-04-18 Update post 1st board checklist.
2022-04-19 Update post board checker.
    Update PCB/Schematic based off feedback from the python checker tool. Also added in a few more ground vias on the RF ground plane to fill in some pour regions.
2022-04-19 Changed the layer stackup ordering.
2022-04-20 Added PROD_IDs to new parts.
2022-04-27 Renamed for release. Some updates post DR.
2022-05-02 Add part, update lib, resize sch parts, bulk brd update.
    Add NLAST SPST switch.
    Update POCI/PICO.
    Make all resistors possible 0402. (Only 10ohm and 68.1k res are still 0603)
2022-05-03 Completed updates post DR.
    Change PPS LED to Yellow.
    U1 make power V_USB, not V_ZED.
    Add PUR on PWR_EN.
    Remove TPs where PTH exists.
    Remove Qwiic connectors.
    Change U1 to be a bigger package.
2022-05-03 Unlocked all components for panelization.
2022-05-03 Removed Acid Traps.
2022-05-04 Update SPST switch with PROD_ID.
2022-05-06 change due to mfgring issue.
    There was no TSTOP on ground pad of U7. Added TSTOP.
2022-05-06 update to v02 for mfgr error.
2022-06-13 Updated footprint for NOT gate.
2022-06-13 v03 protos update.
    Center and update flags.
    Fix RTK STAT circuit.
    Fix voltage divider for USB detect.
    Add I2C PURs.
    Add a PUR for the reset line outside isolation.
    Changed PWR LED resistor to 1k.
2022-06-13 Fixed note font.
2022-06-14 Update post Reds review.
    Line up USB Shield JP with CC resistors.
    Relabel C8 with value, remove tolerance
    Remove cap placement note.
    Make USB Shield JP NC
    Rename JPs to their function
    Add USBSHLD Jumper text
2022-06-14 Added measures on the right side.
2022-06-14 Rev to v10.
2022-06-15 Retune LED brightness.
    Per experiment Pete performed.
    Red LED = 1kOhm @3.3V
    Blue LED = 4.7kOhm @3.3V
    Replaced Yellow LED with Blue LED to match design standards.
2022-06-15 Add Reds Panel.
    Add panel for reds.
2022-07-20 Decrease V_USB vdiv resistors.
    Decrease by 2 orders of magnitude to allow more current flow for V_DETECT.
    22k -> 220
    47k -> 470
2022-08-09 Updated README.md
    Updating README file with photos and links for release.
2023-04-24 Update datasheet
    Adding updated ZED-F9P datasheet.
2023-04-24 Delete ZED-F9P_Data_Sheet.pdf
    Deleting old ZED-F9P datasheet that was replaced by the latest release.
